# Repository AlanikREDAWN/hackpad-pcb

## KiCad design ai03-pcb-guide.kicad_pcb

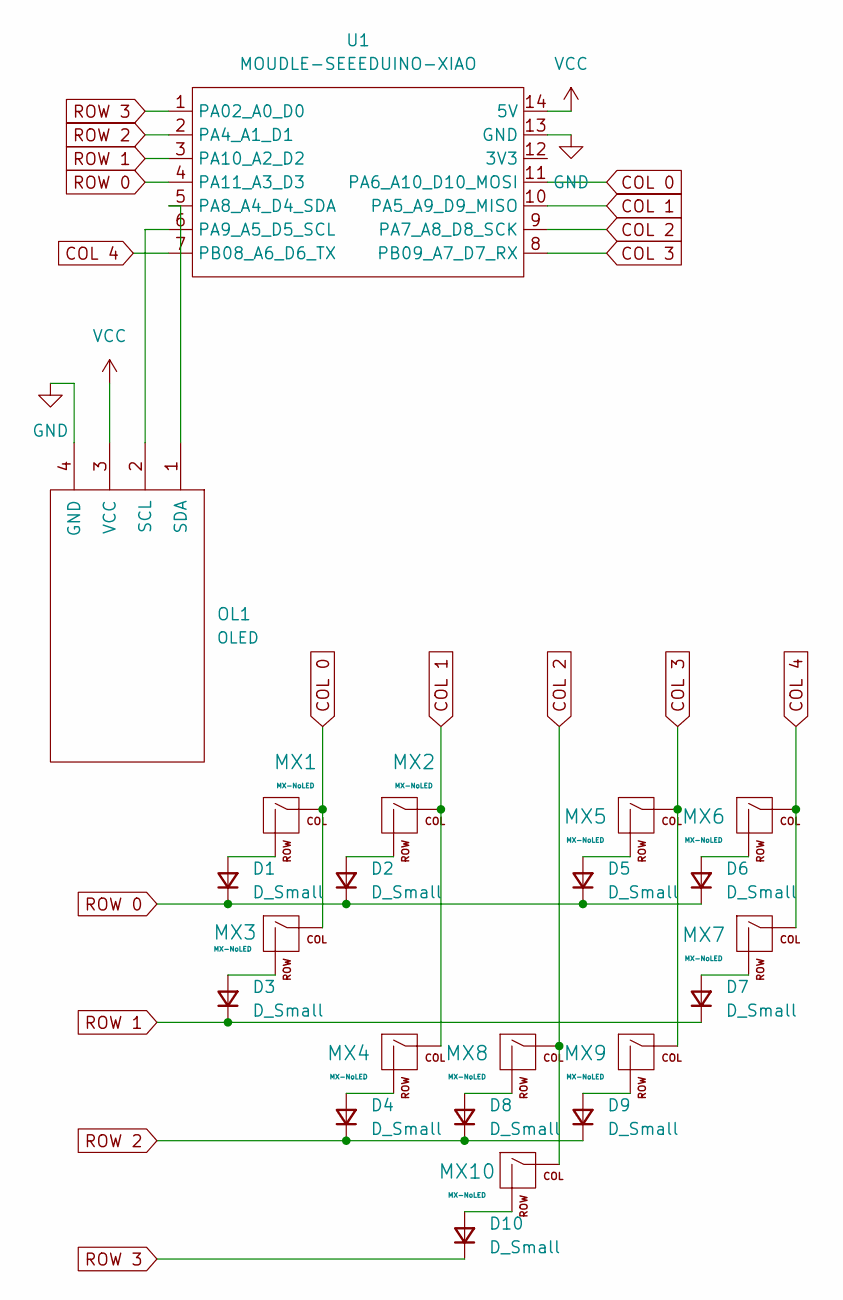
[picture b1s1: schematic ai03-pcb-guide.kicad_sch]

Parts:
D1, D2, D3, D4, D5, D6, D7, D8, D9, D10: D_Small; D_SOD-123
MX1, MX2, MX3, MX4, MX5, MX6, MX7, MX8, MX9, MX10: MX-NoLED; MX-1U-NoLED
OL1: OLED
U1: MOUDLE-SEEEDUINO-XIAO; MOUDLE14P-2.54-21X17.8MM

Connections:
COL 0: MX1.1 (COL), MX3.1 (COL), U1.11 (PA6_A10_D10_MOSI)
COL 1: MX2.1 (COL), MX4.1 (COL), U1.10 (PA5_A9_D9_MISO)
COL 2: MX8.1 (COL), MX10.1 (COL), U1.9 (PA7_A8_D8_SCK)
COL 3: MX5.1 (COL), MX9.1 (COL), U1.8 (PB09_A7_D7_RX)
COL 4: MX6.1 (COL), MX7.1 (COL), U1.7 (PB08_A6_D6_TX)
GND: OL1.4 (GND), U1.13 (GND)
unnamed: D1.2 (A), MX1.2 (ROW)
unnamed: D2.2 (A), MX2.2 (ROW)
unnamed: D3.2 (A), MX3.2 (ROW)
unnamed: D4.2 (A), MX4.2 (ROW)
unnamed: D5.2 (A), MX5.2 (ROW)
unnamed: D6.2 (A), MX6.2 (ROW)
unnamed: D7.2 (A), MX7.2 (ROW)
unnamed: D8.2 (A), MX8.2 (ROW)
unnamed: D9.2 (A), MX9.2 (ROW)
unnamed: D10.2 (A), MX10.2 (ROW)
unnamed: OL1.2 (SCL), U1.6 (PA9_A5_D5_SCL)
unnamed: OL1.1 (SDA), U1.5 (PA8_A4_D4_SDA)
ROW 0: D1.1 (K), D2.1 (K), D5.1 (K), D6.1 (K), U1.4 (PA11_A3_D3)
ROW 1: D3.1 (K), D7.1 (K), U1.3 (PA10_A2_D2)
ROW 2: D4.1 (K), D8.1 (K), D9.1 (K), U1.2 (PA4_A1_D1)
ROW 3: D10.1 (K), U1.1 (PA02_A0_D0)
VCC: OL1.3 (VCC), U1.14 (5V)

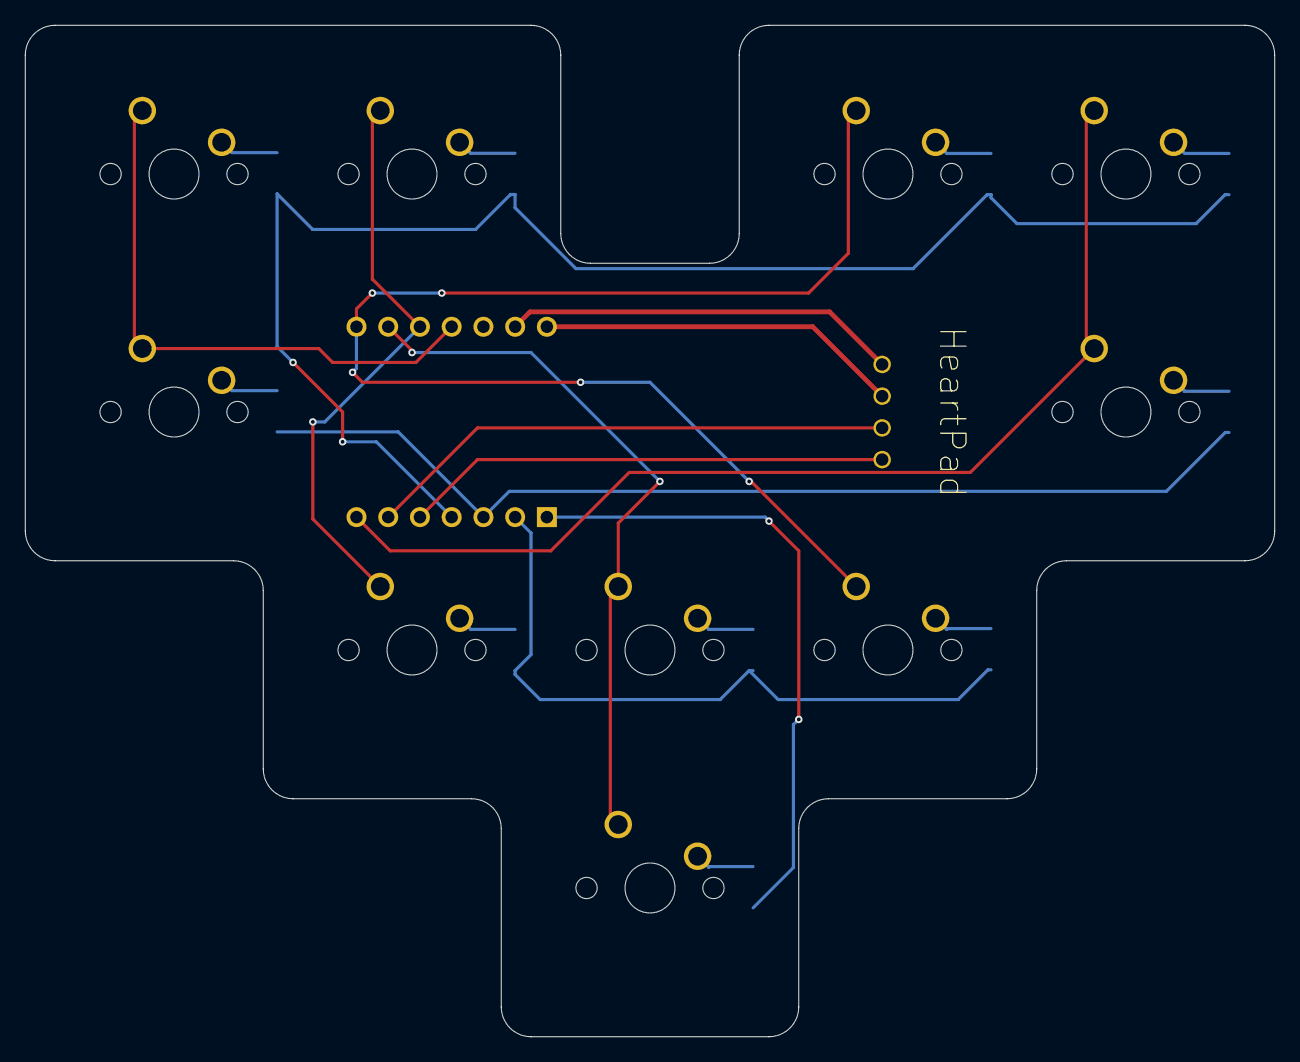
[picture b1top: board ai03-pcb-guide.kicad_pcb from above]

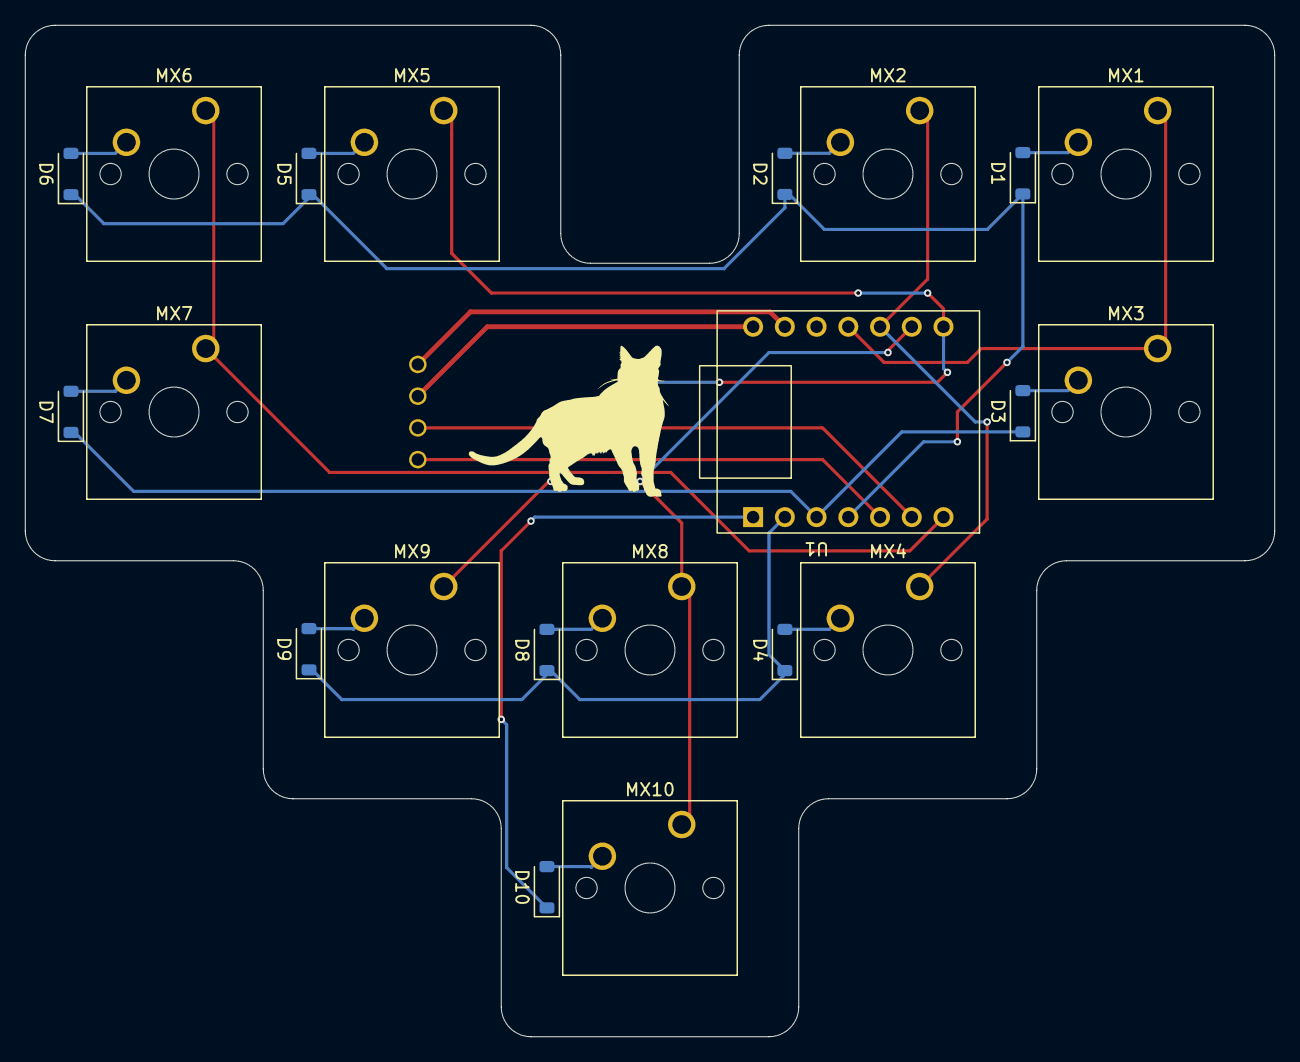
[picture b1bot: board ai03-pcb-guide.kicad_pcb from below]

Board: 2 copper layers, 100.0 x 81.0 mm, 22 parts (21 on the bottom side), 23 nets.

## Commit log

2024-09-15 commit!
2024-09-15 Add submodules
2024-09-15 another commit!
2024-09-15 naooafgdhsdf
2024-09-17 more commit
2024-09-18 i commit
2024-09-18 second commit of the day!
2024-09-24 hackpad progress
2024-09-25 another commit yay
2024-09-25 yayyayysd
2024-10-01 a commit
2024-10-01 added kitty
